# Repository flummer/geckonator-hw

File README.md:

# Geckonator development boards

The Geckonator development boards are a series of tools for working with the USB microgontrollers from Silabs in the Happy Gecko family.

These boards have a very low component count, in part due to the built in features of the controller, eg. built in voltage regulator.

These boards are in part inspired by [Thumbinator][thumbinator] and the [Tomu][tomu] and combines parts from both of these projects.

[thumbinator]: https://github.com/kbeckmann/thumbinator-hw
[tomu]: https://github.com/im-tomu/tomu-hardware

## Hardware
The initial version of the hardware (found in this repository) is a small thumbdrive sized board with a male USB A connector directly on the board and only two LEDs.

The next version ([Geckonator Dev Edition][geckonator-dev]) is a larger board, with a few more components, higher pincount microcontroller and a larger prototyping area for adding other stuff.

[geckonator-dev]: https://github.com/flummer/geckonator-dev

## Firmware

This board is designed for the development of the [Geckoboot bootloader][geckoboot], and for developing applications for this, the [Geckonator][geckonator] repository can be used as a base

[geckoboot]: https://github.com/flummer/geckoboot
[geckonator]: https://github.com/flummer/geckonator

## License

The contents of this repository is released under the following licence:

 * the "Creative Commons Attribution-ShareAlike 4.0 International License"
   (CC BY-SA 4.0) full text of this license is included in the LICENSE file
   and a copy can also be found at
   http://creativecommons.org/licenses/by-sa/4.0/

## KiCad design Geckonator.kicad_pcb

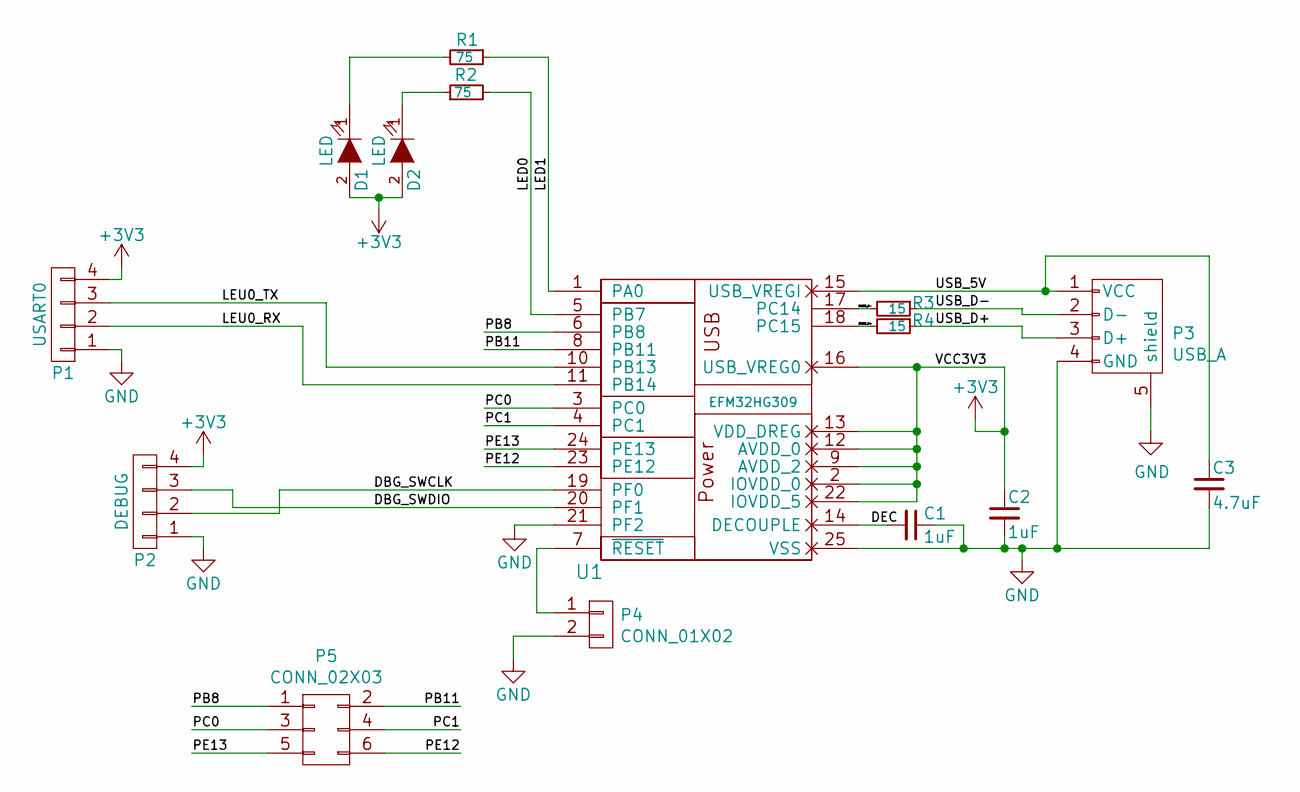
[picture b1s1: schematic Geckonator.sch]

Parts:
C1, C2: 1uF; C_0805_HandSoldering
C3: 4.7uF; C_0805_HandSoldering
D1, D2: LED; LED_0805
P1: USART0; Socket_Strip_Straight_1x04
P2: DEBUG; Socket_Strip_Straight_1x04
P3: USB_A; Molex_0480372200_USB-A_PCB_Male_NO_SLOT
P4: CONN_01X02; Pin_Header_Straight_1x02
P5: CONN_02X03; CONN_2x3_SMD_PADS
R1, R2: 75; R_0805_HandSoldering
R3, R4: 15; R_0805_HandSoldering
U1: EFM32HG309; QFN-24-1EP_5x5mm_Pitch0.65mm

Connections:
+3V3: C2.1, D1.2 (A), D2.2 (A), P1.4, P2.4, U1.2 (IOVDD_0), U1.9 (AVDD_2), U1.12 (AVDD_0), U1.13 (VDD_DREG), U1.16 (USB_VREG0), U1.22 (IOVDD_5)
/DBG_SWCLK: P2.2, U1.19 (PF0)
/DBG_SWDIO: P2.3, U1.20 (PF1)
/DEC: C1.2, U1.14 (DECOUPLE)
/LED0: R2.2, U1.5 (PB7)
/LED1: R1.1, U1.1 (PA0)
/LEU0_RX: P1.2, U1.11 (PB14)
/LEU0_TX: P1.3, U1.10 (PB13)
/PB8: P5.1, U1.6 (PB8)
/PB11: P5.2, U1.8 (PB11)
/PC0: P5.3, U1.3 (PC0)
/PC1: P5.4, U1.4 (PC1)
/PE12: P5.6, U1.23 (PE12)
/PE13: P5.5, U1.24 (PE13)
/RUSB_D+: R4.2, U1.18 (PC15)
/RUSB_D-: R3.2, U1.17 (PC14)
/USB_5V: C3.1, P3.1 (VCC), U1.15 (USB_VREGI)
/USB_D+: P3.3 (D+), R4.1
/USB_D-: P3.2 (D-), R3.1
GND: C1.1, C2.2, C3.2, P1.1, P2.1, P3.4 (GND), P3.5 (shield), P4.2, U1.21 (PF2), U1.25 (VSS)
unnamed: D1.1 (K), R1.2
unnamed: D2.1 (K), R2.1
unnamed: P4.1, U1.7 (~RESET)

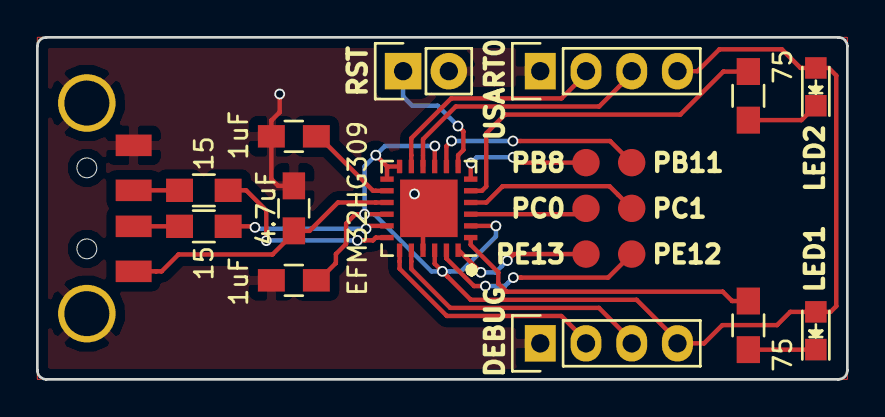
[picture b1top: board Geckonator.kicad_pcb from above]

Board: 2 copper layers, 45.0 x 19.0 mm, 15 parts (0 on the bottom side), 23 nets.

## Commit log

2017-08-01 Initial version of the Geckonator board
2018-04-25 Added license file and description
2018-12-09 Added a bit more information to readme.md
2018-12-09 Added PDF schematic, licensing info and updated to KiCad 5.0
